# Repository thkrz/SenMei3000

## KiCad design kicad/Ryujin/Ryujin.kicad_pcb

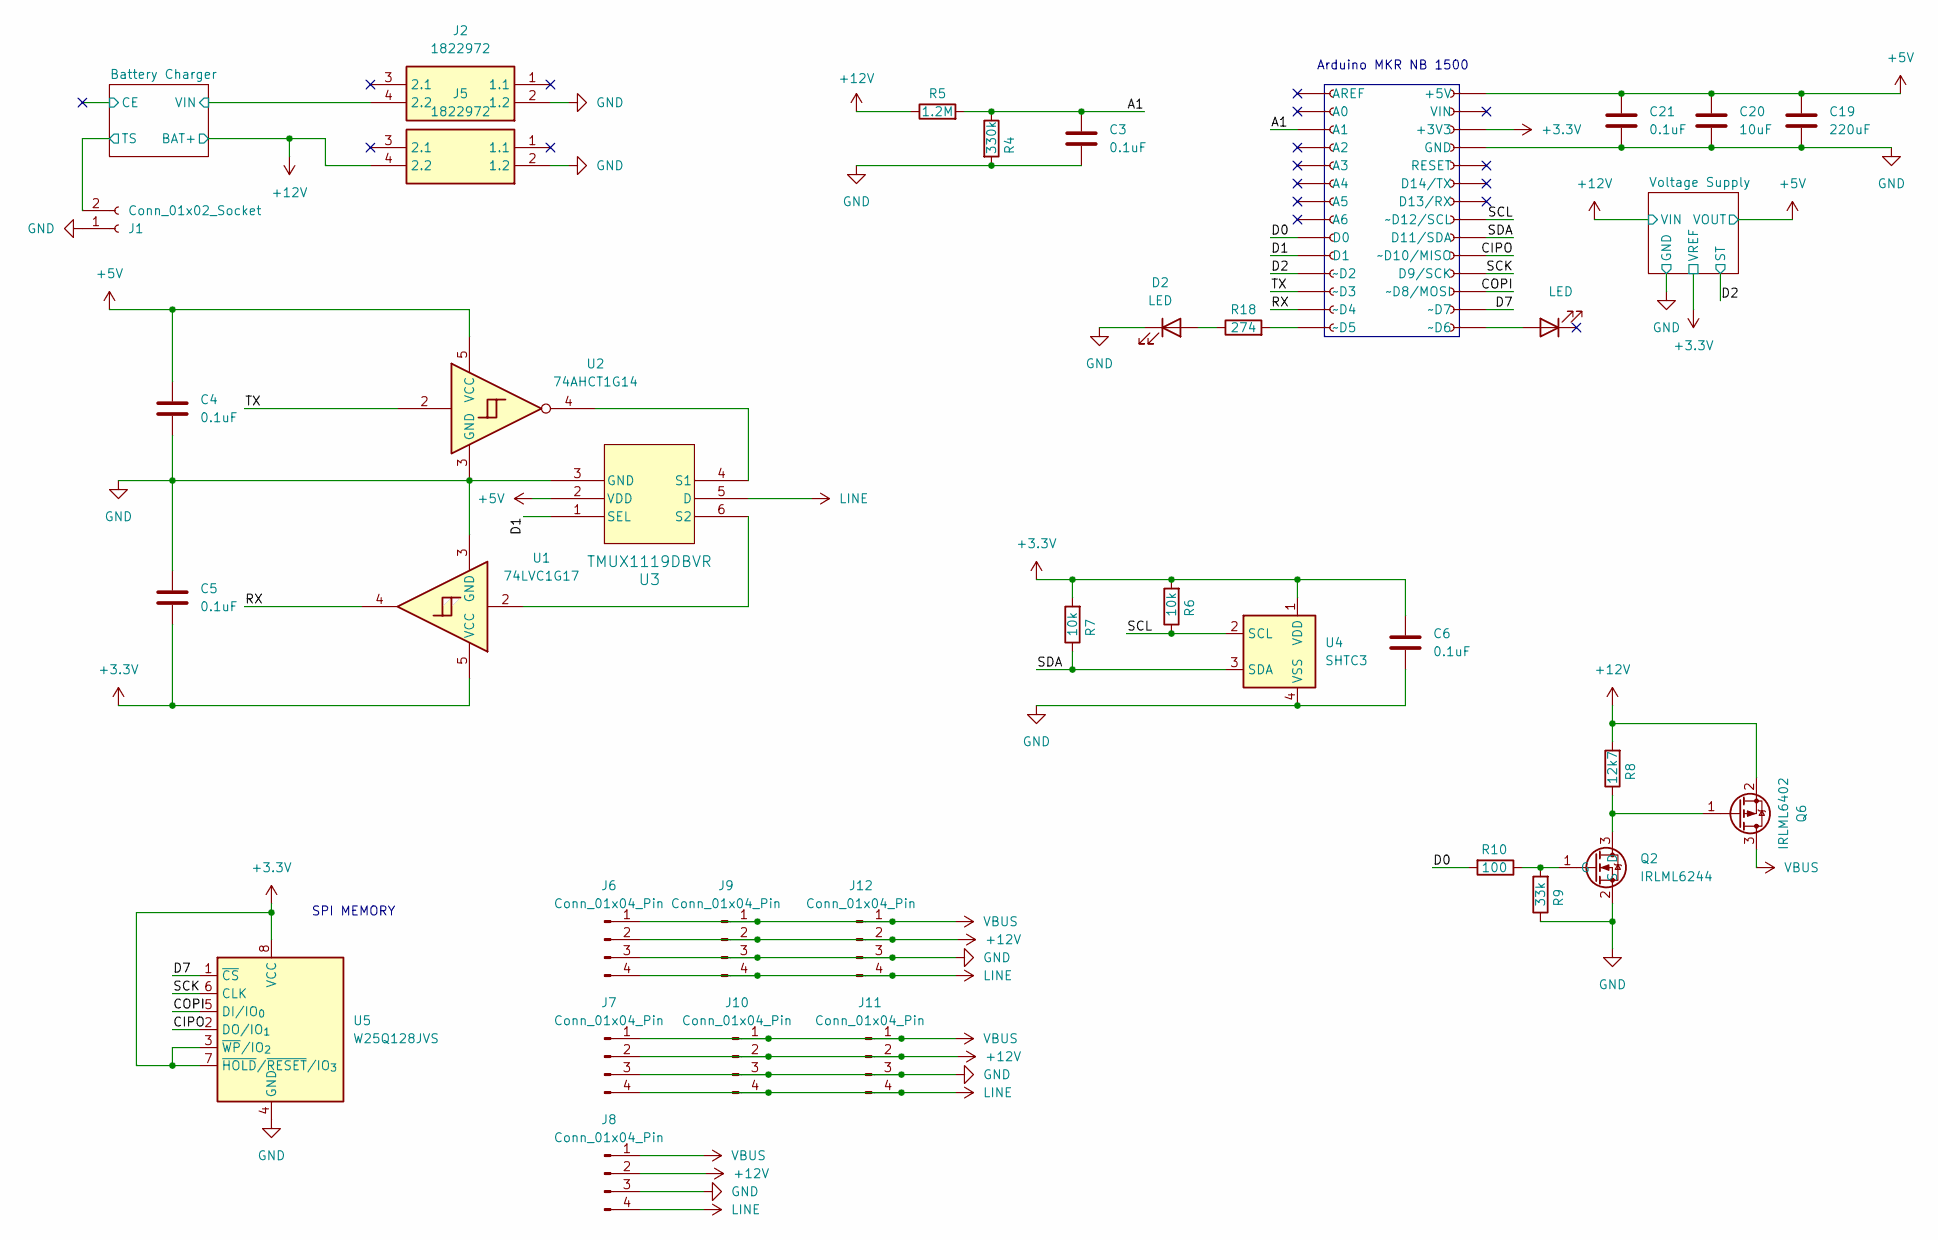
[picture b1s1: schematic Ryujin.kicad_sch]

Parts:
C3, C4, C5, C6, C21: 0.1uF; C_0603_1608Metric; MPN 0.1uF 6.3V 0603
C19: 220uF; EEFCX0J101R; MPN EEFCX0J221R
C20: 10uF; C_0805_2012Metric; MPN 10uF 10V 0805
D2: LED; LED_0603_1608Metric; MPN LTST-C194KFKT
D7: LED; LED_0603_1608Metric
J1: Conn_01x02_Socket; JST_PH_S2B-PH-K_1x02_P2.00mm_Horizontal; MPN S2B-PH-K-S
J2, J5: 1822972; Manufacturer_Part_Number 1822972; Mouser Part Number 651-1822972
J3, J4: Conn_01x14_Socket; 65342372; MPN 6-534237-2
J6, J7, J8, J9, J10, J11, J12: Conn_01x04_Pin; Molex_KK-254_AE-6410-04A_1x04_P2.54mm_Vertical; MPN 22272041
Q2: IRLML6244; SOT-23; MPN IRLML6244TRPBF
Q6: IRLML6402; SOT-23; MPN IRLML6402TRPBF
R4: 330k; R_0603_1608Metric; MPN 330k 0603
R5: 1.2M; R_0603_1608Metric; MPN 1.2M 0603
R6, R7: 10k; R_0603_1608Metric; MPN 10k 0603
R8: 12k7; R_0603_1608Metric; MPN 12.7k 0603
R9: 33k; R_0603_1608Metric; MPN 33k 0603
R10: 100; R_0603_1608Metric; MPN 100 0603
R18: 274; R_0603_1608Metric; MPN 274 0603
U1: 74LVC1G17; SOT-23-5; MPN SN74LVC1G17DBVT
U2: 74AHCT1G14; SOT-23-5; MPN SN74AHCT1G14DBVR
U3: TMUX1119DBVR; TMUXDBVR
U4: SHTC3; Sensirion_DFN-4-1EP_2x2mm_P1mm_EP0.7x1.6mm; MPN SHTC3
U5: W25Q128JVS; SOIC-8_5.3x5.3mm_P1.27mm; MPN W25Q128JVSIQ TR

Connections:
+3.3V: C5.2, C6.1, J4.3 (+3V3), R6.2, R7.2, U1.5 (VCC), U4.1 (VDD), U5.3 (~WP/IO_{2}), U5.7 (~HOLD/~RESET/IO_{3}), U5.8 (VCC); also elsewhere on the board
+5V: C4.1, C19.1, C20.1, C21.1, J4.1 (+5V), U2.5 (VCC), U3.2 (VDD); also elsewhere on the board
+12V: J5.4 (2.2), J6.2, J7.2, J8.2, J9.2, J10.2, J11.2, J12.2, Q6.2 (S), R5.1, R8.2; also elsewhere on the board
/A1: C3.1, J3.3 (A1), R4.1, R5.2
/Battery Charger/TS: J1.2; also elsewhere on the board
/Battery Charger/VIN: J2.4 (2.2); also elsewhere on the board
/CIPO: J4.10 (~D10/MISO), U5.2 (DO/IO_{1})
/COPI: J4.12 (~D8/MOSI), U5.5 (DI/IO_{0})
/D0: J3.9 (D0), R10.2
/D1: J3.10 (D1), U3.1 (SEL)
/D2: J3.11 (~D2); also elsewhere on the board
/D7: J4.13 (~D7), U5.1 (~CS)
/RX: J3.13 (~D4), U1.4
/SCK: J4.11 (D9/SCK), U5.6 (CLK)
/SCL: J4.8 (~D12/SCL), R6.1, U4.2 (SCL)
/SDA: J4.9 (D11/SDA), R7.1, U4.3 (SDA)
/TX: J3.12 (~D3), U2.2
GND: C3.2, C4.2, C5.1, C6.2, C19.2, C20.2, C21.2, D2.1 (K), J1.1, J2.2 (1.2), J4.4 (GND), J5.2 (1.2), J6.3, J7.3, J8.3, J9.3, J10.3, J11.3, J12.3, Q2.2 (S), R4.2, R9.1, U1.3 (GND), U2.3 (GND), U3.3 (GND), U4.4 (VSS), U5.4 (GND); also elsewhere on the board
LINE: J6.4, J7.4, J8.4, J9.4, J10.4, J11.4, J12.4, U3.5 (D)
unnamed: D2.2 (A), R18.1
unnamed: J3.14 (~D5), R18.2
unnamed: D7.2 (A), J4.14 (~D6)
unnamed: Q2.3 (D), Q6.1 (G), R8.1
unnamed: Q2.1 (G), R9.2, R10.1
unnamed: U2.4, U3.4 (S1)
unnamed: U1.2, U3.6 (S2)
VBUS: J6.1, J7.1, J8.1, J9.1, J10.1, J11.1, J12.1, Q6.3 (D)

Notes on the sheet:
SPI MEMORY
Arduino MKR NB 1500

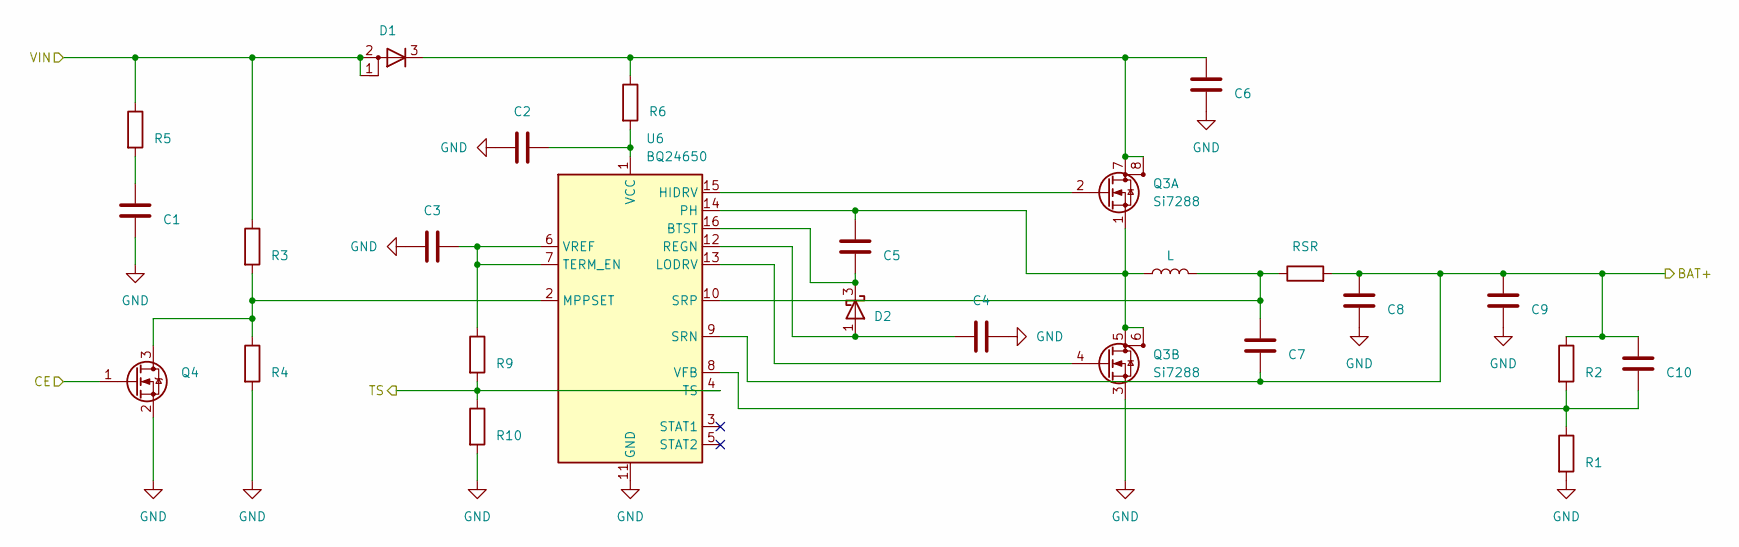
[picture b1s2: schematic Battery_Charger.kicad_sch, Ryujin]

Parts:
C7: C1; C_1210_3225Metric; MPN 2.2uF 50V 1210
C8: C2; C_0805_2012Metric; MPN 1uF 35V 0805
C9: C6; C_1210_3225Metric; MPN 10uF 35V 1210
C10: C4; C_0805_2012Metric; MPN 1uF 35V 0805
C11: C5; C_0805_2012Metric; MPN C0805C104K6RACTU
C12: C8; C_1210_3225Metric; MPN 10uF 35V 1210
C13: C7; C_0805_2012Metric; MPN C0805C104K6RACTU
C14: C10; C_0603_1608Metric; MPN 22pF 50V 0603
C15: C3; C_0805_2012Metric; MPN 1uF 35V 0805
C16: C9; C_Elec_4x5.4; MPN EEEFK1V4R7AR
D5: D1; PDS104013; MPN PDS1040-13
D6: D2; SOT-23; MPN BAT54
L1: L; L_Vishay_IHLP-2525; MPN IHLP2525CZER100MA1
Q3: Si7288; SI7288DPT1GE3; MPN SI7288DP-T1-GE3
Q4: 2N7002; SOT-23
R1: R5; R_2512_6332Metric; MPN 2 5% 1W
R2: R3; R_0402_1005Metric; MPN 499k 0402
R3: R4; R_0402_1005Metric; MPN 36k 0402
R13: R6; R_1206_3216Metric; MPN 10 1206 0.25W
R14: R9; R_0402_1005Metric; MPN 5.23k 0402
R15: R1; R_0402_1005Metric; MPN 97.6k 0402
R16: R2; R_0402_1005Metric; MPN 536k 0402
R17: R10; R_0402_1005Metric; MPN 30.1k 0402
RSR1: RSR; R_1206_3216Metric; MPN WSL1206R0200DEA
U6: BQ24650; Texas_RVA_VQFN-16-1EP_3.5x3.5mm_P0.5mm_EP2.14x2.14mm_Therma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; MPN BQ24650RVAR

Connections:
+12V: C12.1, C13.1, C14.1, C16.1, R16.1, RSR1.2, U6.9 (SRN); also elsewhere on the board
/Battery Charger/TS: R14.2, R17.1, U6.4 (TS); also elsewhere on the board
/Battery Charger/VIN: D5.1 (A), D5.2 (A), R1.1, R2.1; also elsewhere on the board
GND: C7.2, C8.1, C9.2, C10.2, C12.2, C15.1, C16.2, Q3.3 (S), Q4.2 (S), R3.2, R15.2, R17.2, U6.11 (GND), U6.17 (GND); also elsewhere on the board
unnamed: C7.1, R1.2
unnamed: C9.1, D5.3 (K), Q3.7 (D), Q3.8 (D), Q3.9 (D), Q3.11 (D), R13.1
unnamed: C10.1, D6.1 (A), U6.12 (REGN)
unnamed: C11.1, D6.3 (K), U6.16 (BTST)
unnamed: Q3.2 (G), U6.15 (HIDRV)
unnamed: C11.2, L1.1, Q3.1 (S), Q3.5 (D), Q3.6 (D), Q3.10 (D), Q3.12 (D), U6.14 (PH)
unnamed: Q3.4 (G), U6.13 (LODRV)
unnamed: Q4.3 (D), R2.2, R3.1, U6.2 (MPPSET)
unnamed: C13.2, L1.2, RSR1.1, U6.10 (SRP)
unnamed: C15.2, R14.1, U6.6 (VREF), U6.7 (TERM_EN)
unnamed: C8.2, R13.2, U6.1 (VCC)
unnamed: C14.2, R15.1, R16.2, U6.8 (VFB)

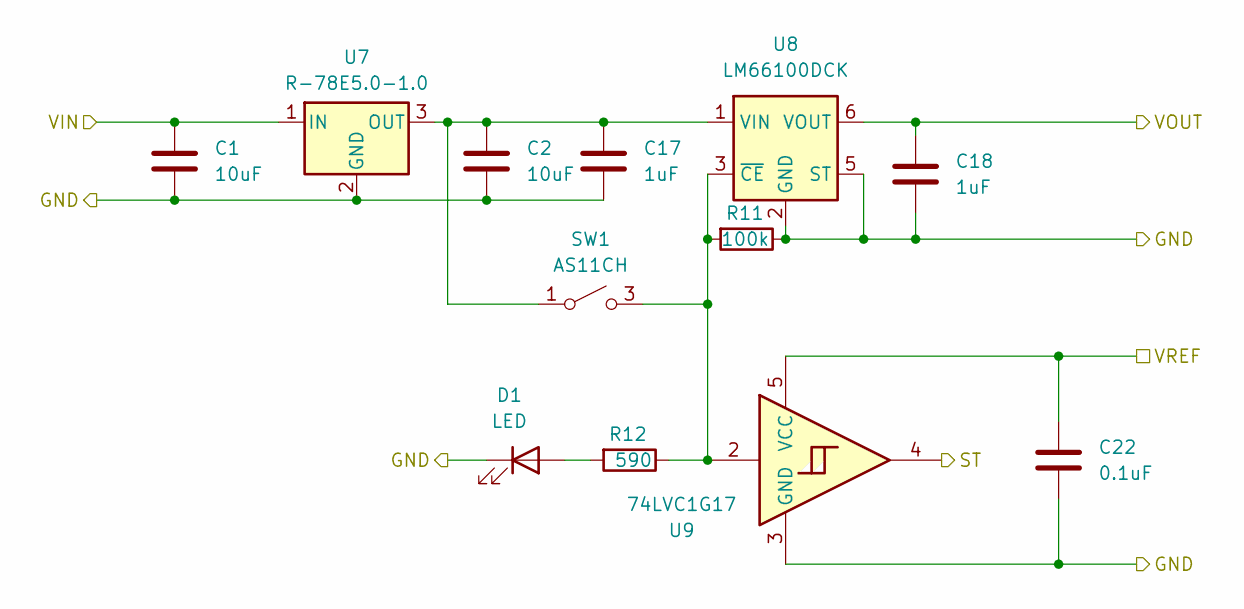
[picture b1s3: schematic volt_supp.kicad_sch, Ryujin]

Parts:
C1: 10uF; C_1206_3216Metric; MPN 10uF 16V 1206
C2: 10uF; C_0805_2012Metric; MPN 10uF 6.3V 0805
C17, C18: 1uF; C_0603_1608Metric; MPN 1uF 6.3V 0603
C22: 0.1uF; C_0603_1608Metric; MPN 0.1uF 6.3V 0603
D1: LED; LED_0603_1608Metric; MPN LTST-C193KRKT-5A
R11: 100k; R_0603_1608Metric; MPN 100k 0603
R12: 590; R_0603_1608Metric; MPN 590 0603
SW1: AS11CH
U7: R-78E5.0-1.0; Converter_DCDC_RECOM_R-78E-0.5_THT
U8: LM66100DCK; SOT-363_SC-70-6; MPN LM66100DCKT
U9: 74LVC1G17; SOT-23-5; MPN SN74LVC1G17DBVT

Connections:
+3.3V: C22.2, U9.5 (VCC); also elsewhere on the board
+5V: C18.1, U8.6 (VOUT); also elsewhere on the board
+12V: C1.1, U7.1 (IN); also elsewhere on the board
/D2: U9.4; also elsewhere on the board
GND: C1.2, C2.2, C17.2, C18.2, C22.1, D1.1 (K), R11.1, U7.2 (GND), U8.2 (GND), U8.5 (ST), U9.3 (GND); also elsewhere on the board
unnamed: D1.2 (A), R12.2
unnamed: C2.1, C17.1, SW1.1 (A), U7.3 (OUT), U8.1 (VIN)
unnamed: R11.2, R12.1, SW1.3 (B), U8.3 (~CE), U9.2

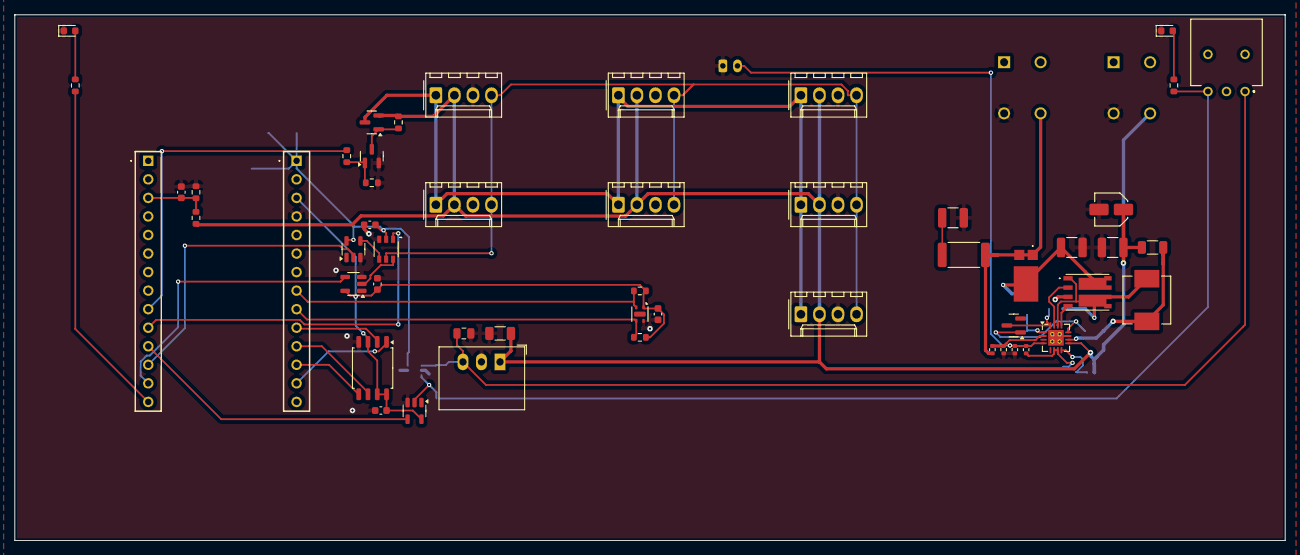
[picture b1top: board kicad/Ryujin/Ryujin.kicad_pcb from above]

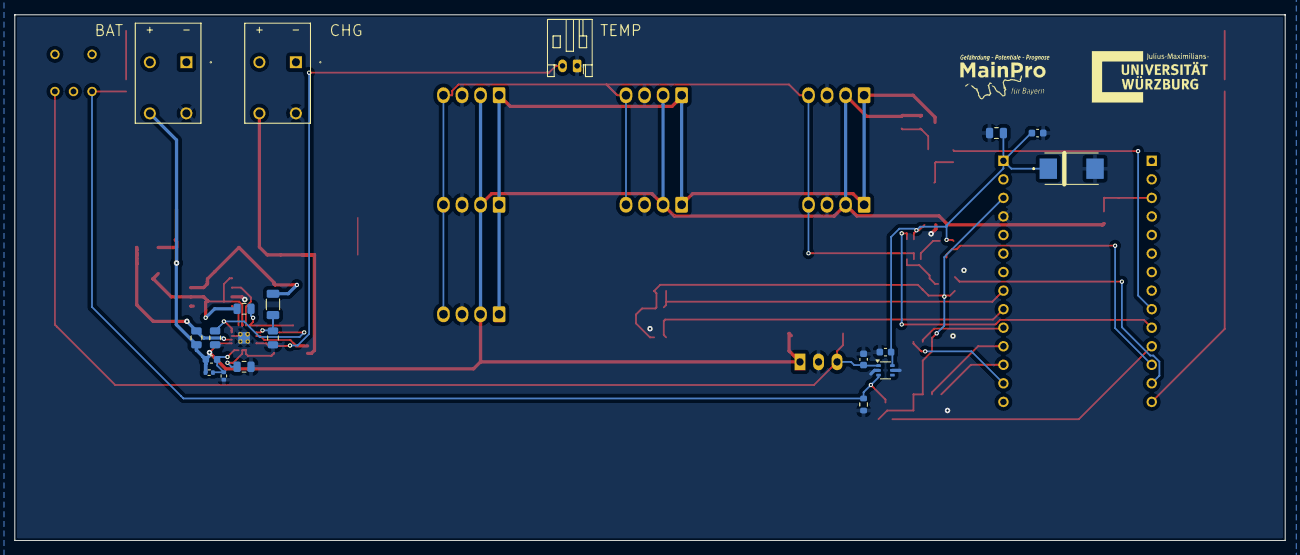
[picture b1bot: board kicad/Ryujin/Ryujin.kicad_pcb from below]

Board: 2 copper layers, 174.0 x 72.0 mm, 73 parts (21 on the bottom side), 41 nets.

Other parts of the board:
G1, G2: LOGO

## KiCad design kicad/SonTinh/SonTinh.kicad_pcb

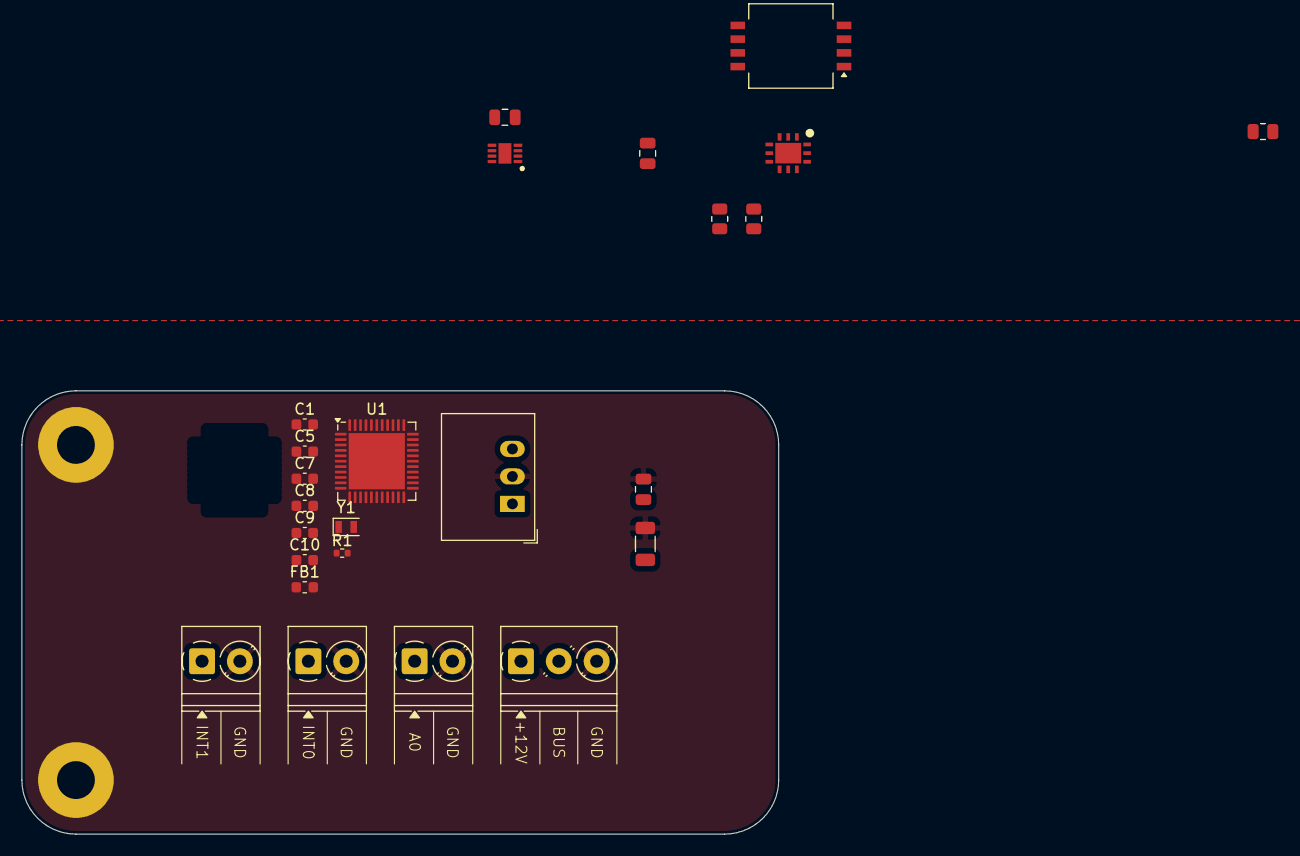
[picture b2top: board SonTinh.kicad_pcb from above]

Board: 2 copper layers, 70.0 x 41.0 mm, 27 parts (0 on the bottom side), 10 nets, no tracks yet.

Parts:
C1, C5, C7, C8, C9, C10: C; C_0603_1608Metric
C2, C6: C; C_0805_2012Metric
C3: 10uF; C_1206_3216Metric
C4: 10uF; C_0805_2012Metric
FB1: FerriteBead; L_0603_1608Metric
H1, H2: MountingHole_Pad; MountingHole_3.5mm_Pad
IC1: SHT35-DIS-F2.5kS; SON50P250X250X100-9N-D
IC2: STC31-C-R3; QFN80P300X350X110-13N-D
J1, J2, J3: Screw_Terminal_01x02; TerminalBlock_Phoenix_PT-1,5-2-3.5-H_1x02_P3.50mm_Horizontal
J4: Screw_Terminal_01x03; TerminalBlock_Phoenix_PT-1,5-3-3.5-H_1x03_P3.50mm_Horizontal
R1: R; R_0402_1005Metric
R13: 100k; R_0805_2012Metric
R14, R15: 10k; R_0805_2012Metric
U1: ATmega32U4-M; QFN-44-1EP_7x7mm_P0.5mm_EP5.2x5.2mm
U3: MPXH6115A; Freescale_98ARH99066A
U7: R-78E5.0-1.0; Converter_DCDC_RECOM_R-78E-0.5_THT
Y1: Crystal; Crystal_SMD_2012-2Pin_2.0x1.2mm

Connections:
+5V: C2.2, C4.1, C6.2, IC1.5 (VDD), IC2.6 (VDD), R14.2, R15.2, U3.2 (Vcc), U7.3 (OUT)
+12V: C3.1, J4.1, U7.1 (IN)
/D7: J4.2, R13.2
/MCU/GND: C1.2, C5.2, C7.2, C8.2, C9.2, C10.2, R1.1, U1.5 (UGND), U1.15 (GND), U1.23 (GND), U1.35 (GND), U1.43 (GND), U1.45 (GND)
/MCU/VCC: C1.1, C5.1, C7.1, C8.1, C10.1, FB1.1, FB1.2, U1.2 (UVCC), U1.14 (VCC), U1.24 (AVCC), U1.34 (VCC), U1.44 (AVCC)
/SCL_5V: IC1.4 (SCL), IC2.4 (SCL), R14.1
/SDA_5V: IC1.1 (SDA), IC2.7 (SDA), R15.1
GND: C2.1, C3.2, C4.2, C6.1, H1.1, H2.1, IC1.2 (ADDR), IC1.7 (R), IC1.8 (VSS), IC1.9 (EP), IC2.1 (VSS_1), IC2.3 (ADDR), IC2.5 (VSS_2), IC2.9 (VSS_3), IC2.11 (VSS_4), IC2.13 (EP), J1.2, J2.2, J3.2, J4.3, R13.1, U3.3 (GND), U7.2 (GND)
unnamed: C9.1, U1.42 (AREF)
unnamed: R1.2, U1.13 (~RESET)

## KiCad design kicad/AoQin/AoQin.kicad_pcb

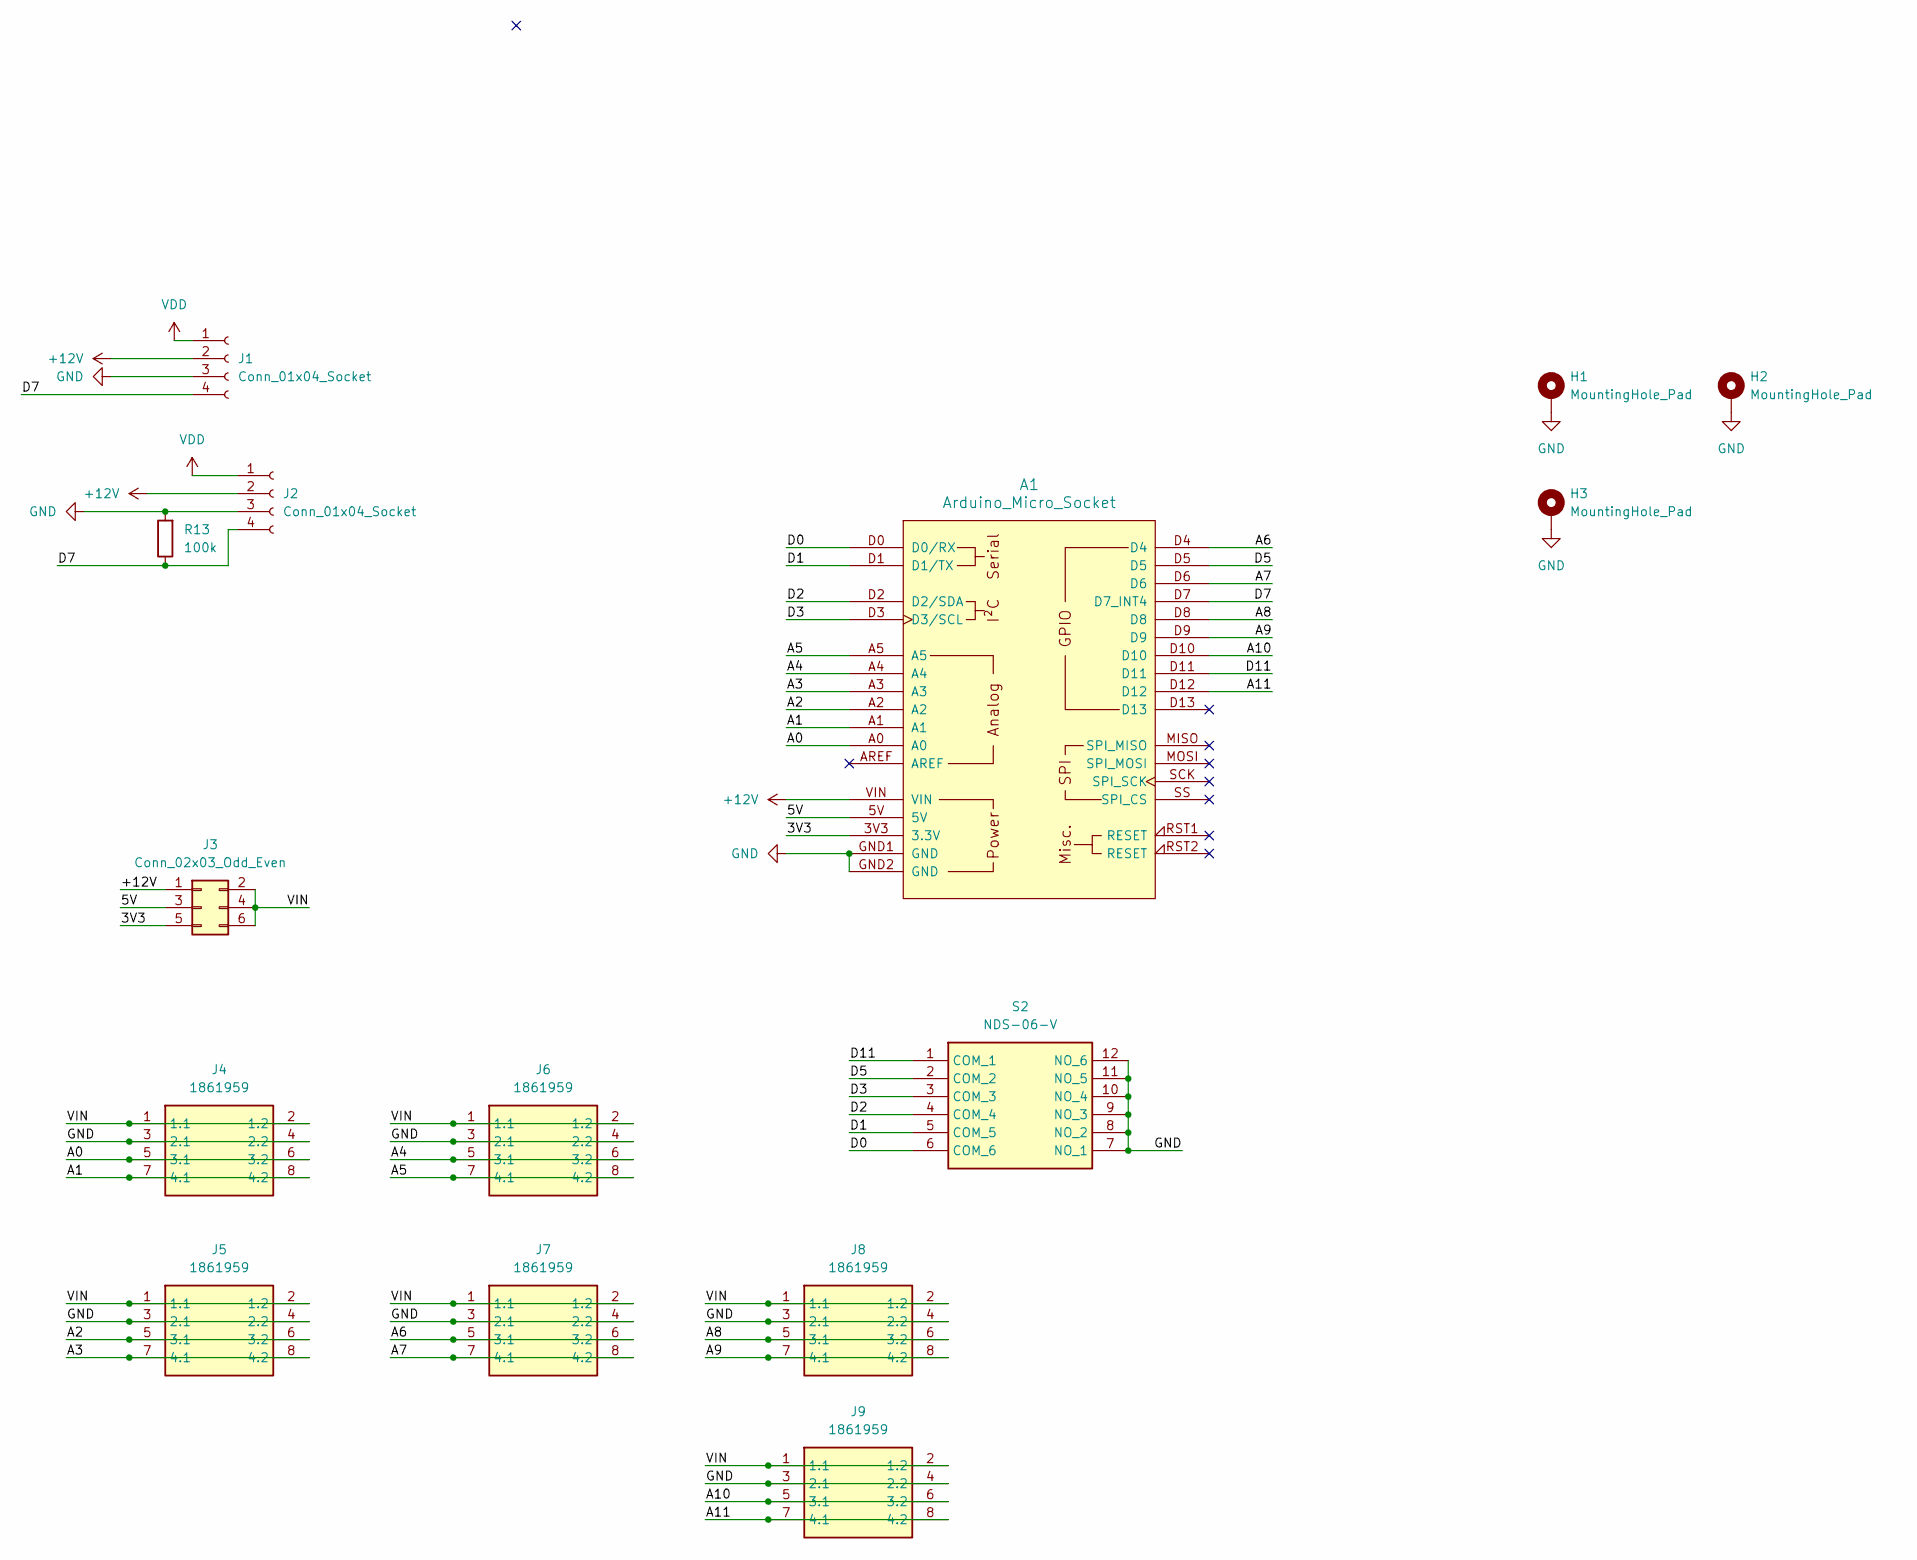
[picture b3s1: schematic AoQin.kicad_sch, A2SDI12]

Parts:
A1: Arduino_Micro_Socket
H1, H2, H3: MountingHole_Pad; MountingHole_3.5mm_Pad
J1, J2: Conn_01x04_Socket; SolderWire-0.5sqmm_1x04_P4.6mm_D0.9mm_OD2.1mm
J3: Conn_02x03_Odd_Even; PinHeader_2x03_P2.54mm_Vertical
J4, J5, J6, J7, J8, J9: 1861959; Manufacturer_Part_Number 1861959; Mouser Part Number 651-1861959
R13: 100k; R_Axial_DIN0204_L3.6mm_D1.6mm_P7.62mm_Horizontal; MPN 100k
S2: NDS-06-V; NDS06V; Manufacturer_Part_Number NDS-06-V; Mouser Part Number N/A

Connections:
+12V: A1.VIN, J1.2, J2.2, J3.1
/3V3: A1.3V3 (3.3V), J3.5
/5V: A1.5V, J3.3
/A0: A1.A0, J4.5 (3.1), J4.6 (3.2)
/A1: A1.A1, J4.7 (4.1), J4.8 (4.2)
/A2: A1.A2, J5.5 (3.1), J5.6 (3.2)
/A3: A1.A3, J5.7 (4.1), J5.8 (4.2)
/A4: A1.A4, J6.5 (3.1), J6.6 (3.2)
/A5: A1.A5, J6.7 (4.1), J6.8 (4.2)
/A6: A1.D4, J7.5 (3.1), J7.6 (3.2)
/A7: A1.D6, J7.7 (4.1), J7.8 (4.2)
/A8: A1.D8, J8.5 (3.1), J8.6 (3.2)
/A9: A1.D9, J8.7 (4.1), J8.8 (4.2)
/A10: A1.D10, J9.5 (3.1), J9.6 (3.2)
/A11: A1.D12, J9.7 (4.1), J9.8 (4.2)
/D0: A1.D0 (D0/RX), S2.6 (COM_6)
/D1: A1.D1 (D1/TX), S2.5 (COM_5)
/D2: A1.D2 (D2/SDA), S2.4 (COM_4)
/D3: A1.D3 (D3/SCL), S2.3 (COM_3)
/D5: A1.D5, S2.2 (COM_2)
/D7: A1.D7 (D7_INT4), J1.4, J2.4, R13.1
/D11: A1.D11, S2.1 (COM_1)
/VIN: J3.2, J3.4, J3.6, J4.1 (1.1), J4.2 (1.2), J5.1 (1.1), J5.2 (1.2), J6.1 (1.1), J6.2 (1.2), J7.1 (1.1), J7.2 (1.2), J8.1 (1.1), J8.2 (1.2), J9.1 (1.1), J9.2 (1.2)
GND: A1.GND1 (GND), A1.GND2 (GND), H1.1, H2.1, H3.1, J1.3, J2.3, J4.3 (2.1), J4.4 (2.2), J5.3 (2.1), J5.4 (2.2), J6.3 (2.1), J6.4 (2.2), J7.3 (2.1), J7.4 (2.2), J8.3 (2.1), J8.4 (2.2), J9.3 (2.1), J9.4 (2.2), R13.2, S2.7 (NO_1), S2.8 (NO_2), S2.9 (NO_3), S2.10 (NO_4), S2.11 (NO_5), S2.12 (NO_6)
VDD: J1.1, J2.1

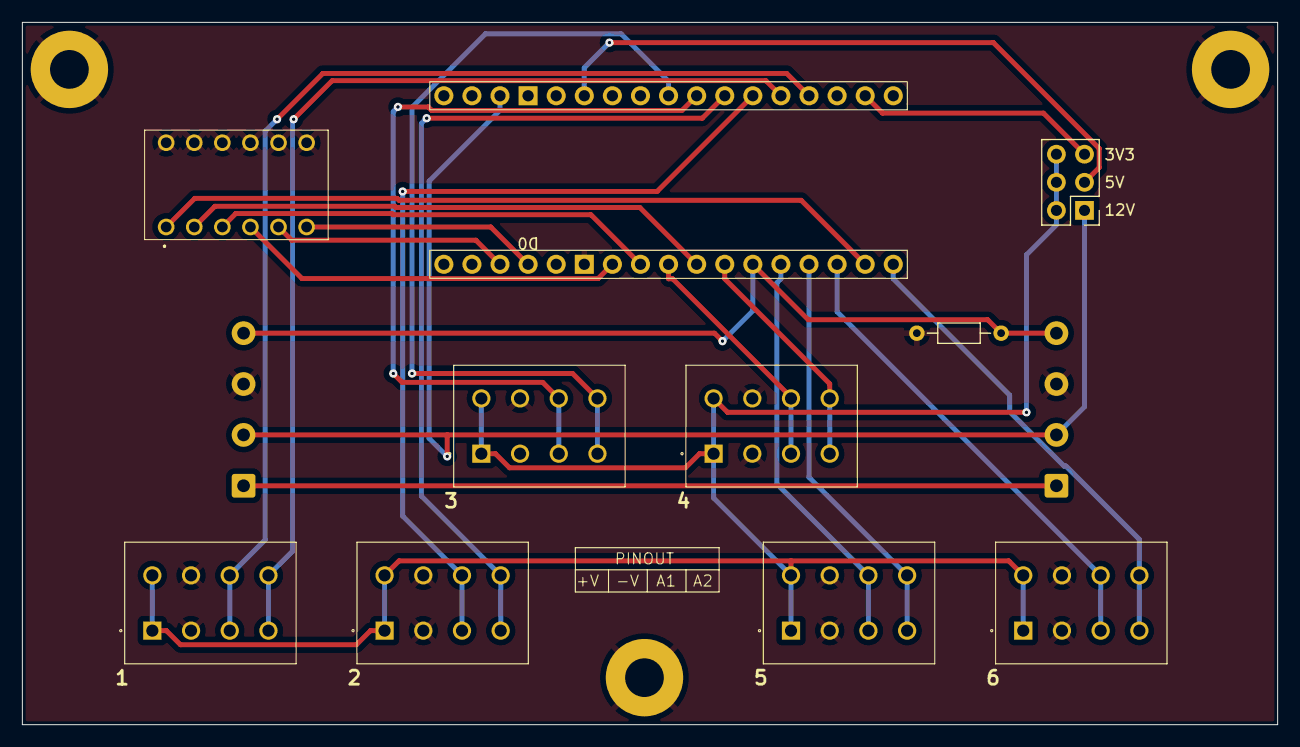
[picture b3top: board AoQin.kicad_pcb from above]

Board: 2 copper layers, 113.5 x 63.5 mm, 15 parts (0 on the bottom side), 25 nets.

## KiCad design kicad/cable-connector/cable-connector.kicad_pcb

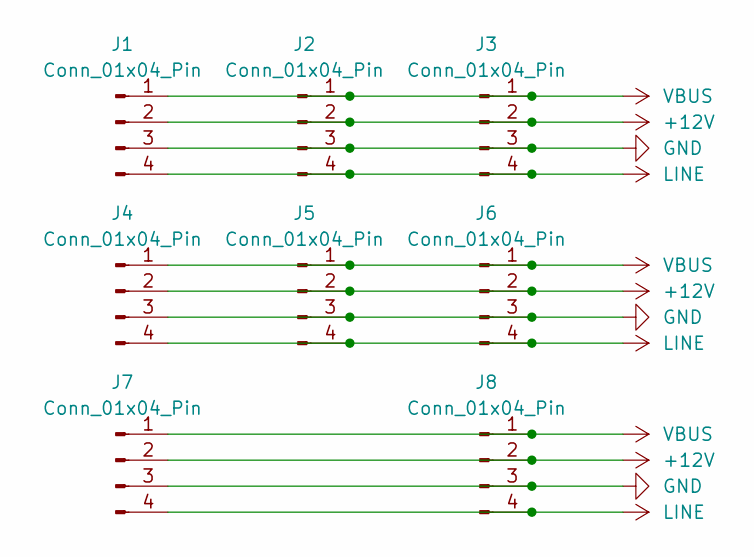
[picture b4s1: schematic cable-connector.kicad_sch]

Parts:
J1, J2, J3, J4, J5, J6, J7: Conn_01x04_Pin; SDI_Connector
J8: Conn_01x04_Pin; GROVE-HW4-2.0

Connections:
+12V: J1.2, J2.2, J3.2, J4.2, J5.2, J6.2, J7.2, J8.2
GND: J1.3, J2.3, J3.3, J4.3, J5.3, J6.3, J7.3, J8.3
LINE: J1.4, J2.4, J3.4, J4.4, J5.4, J6.4, J7.4, J8.4
VBUS: J1.1, J2.1, J3.1, J4.1, J5.1, J6.1, J7.1, J8.1

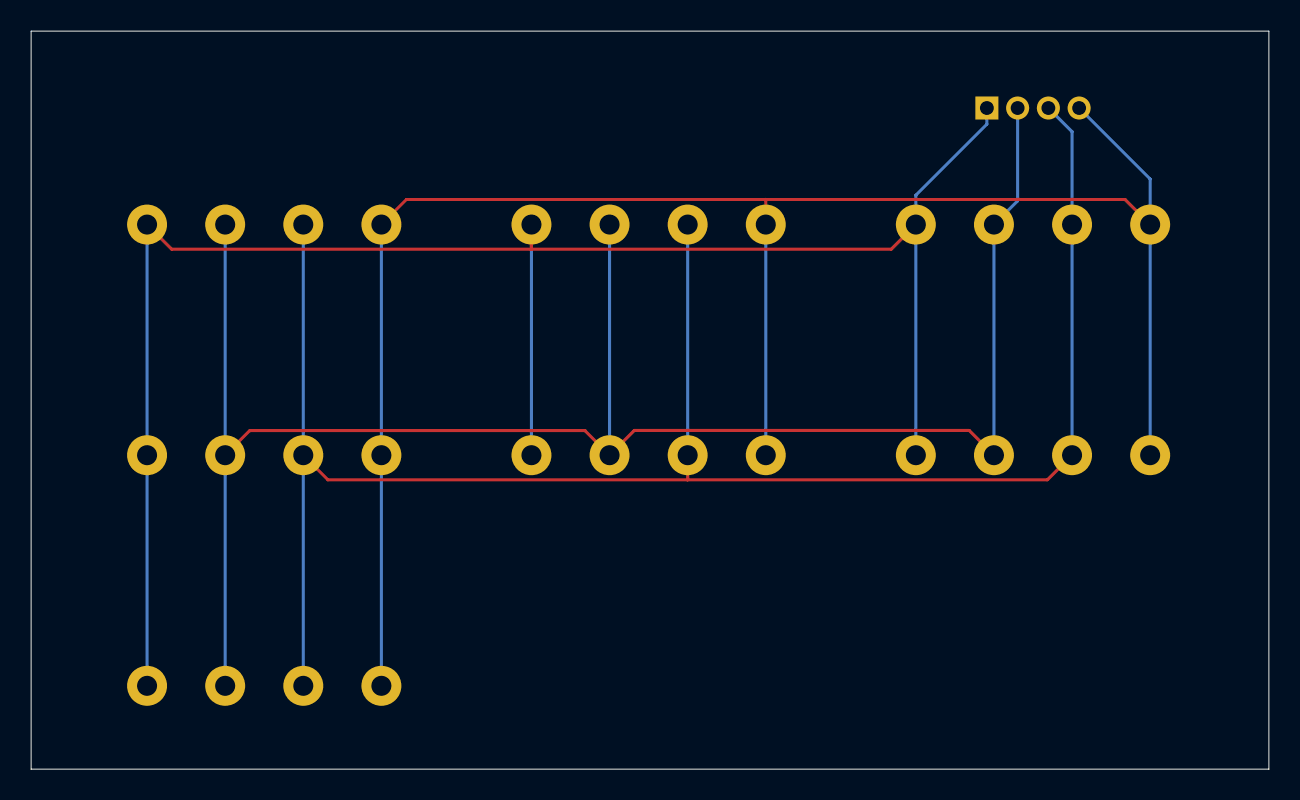
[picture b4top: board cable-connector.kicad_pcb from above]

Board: 2 copper layers, 80.5 x 48.0 mm, 8 parts (1 on the bottom side), 4 nets.

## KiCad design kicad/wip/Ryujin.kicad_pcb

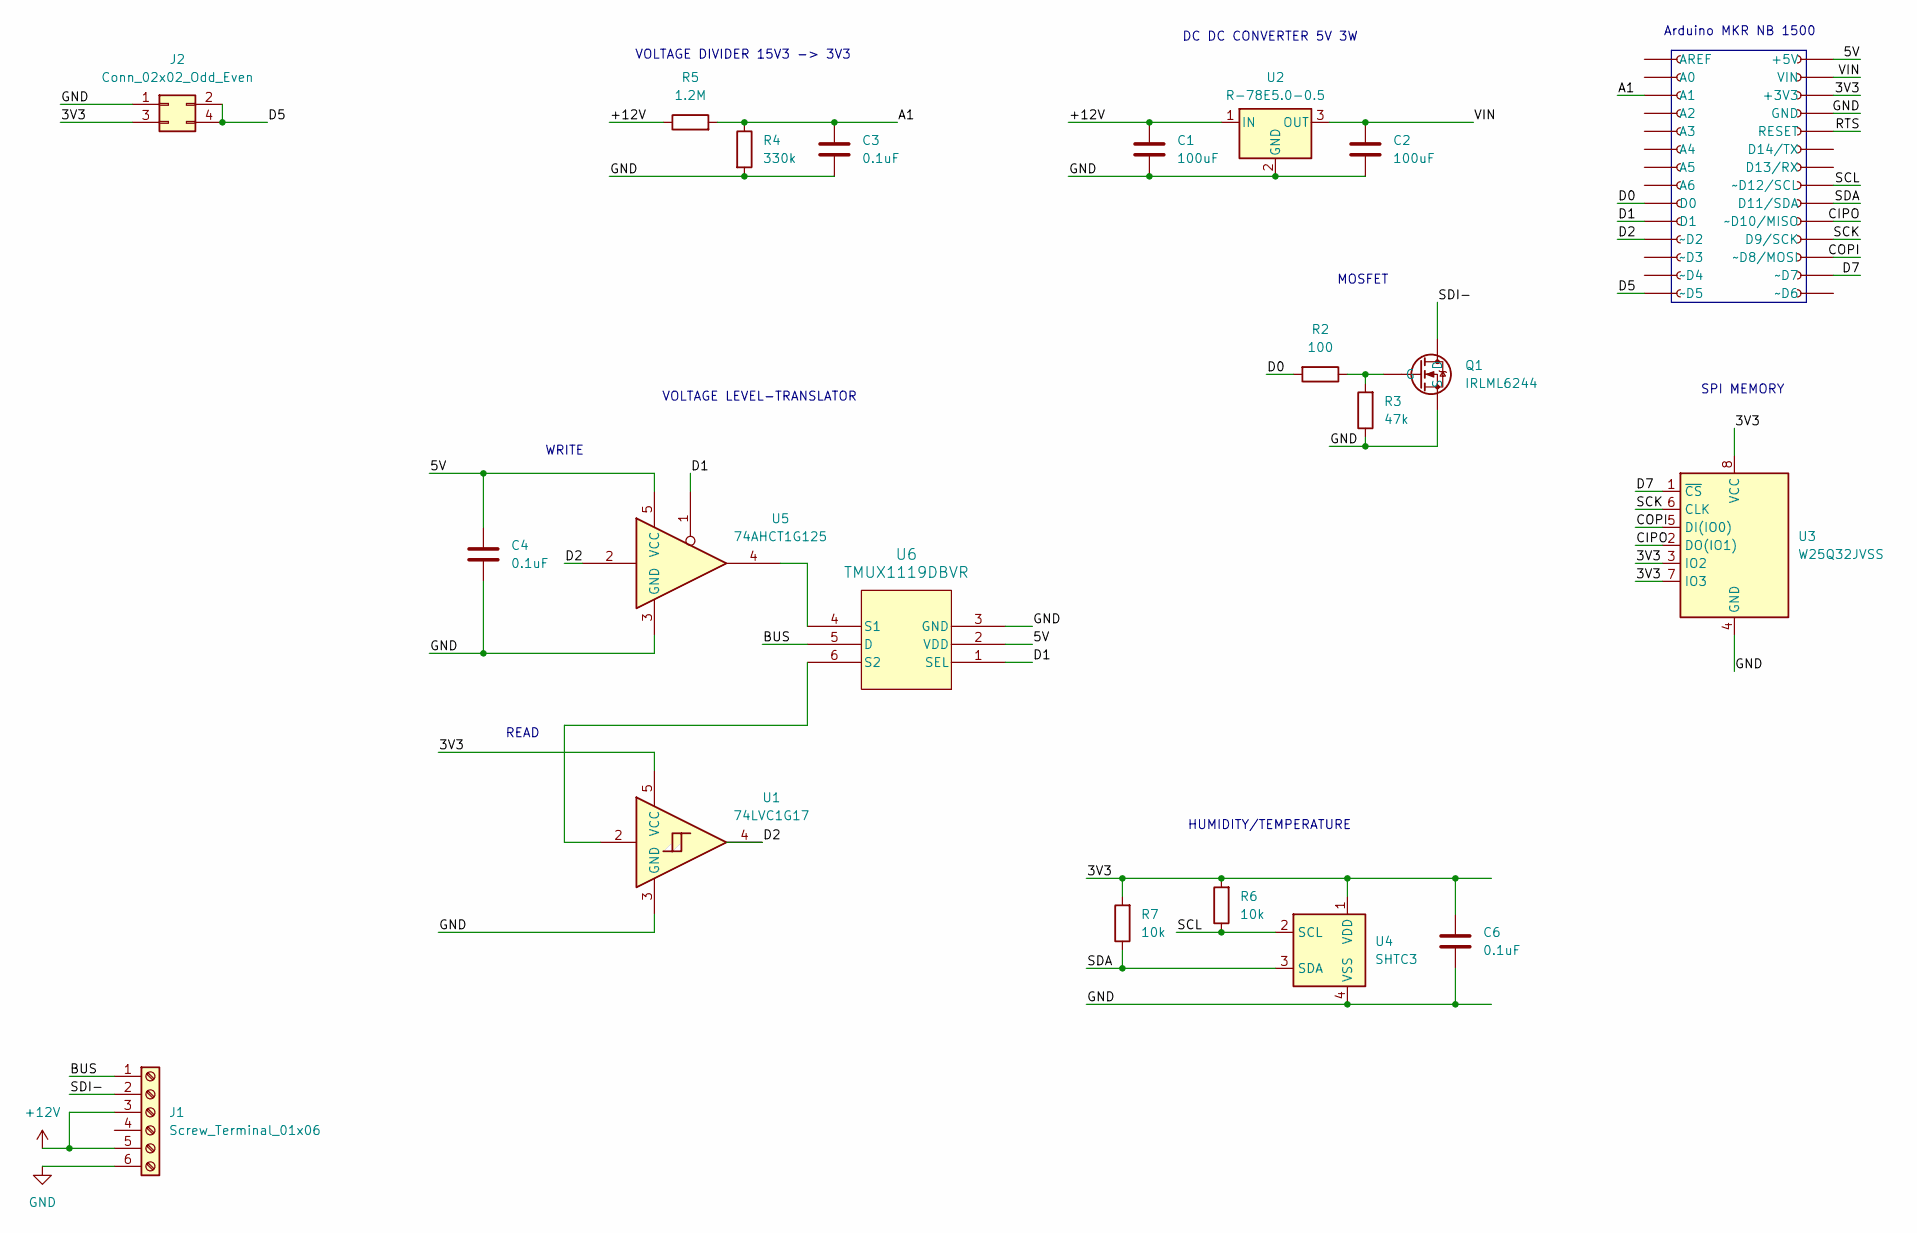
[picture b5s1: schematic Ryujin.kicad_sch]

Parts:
C1: 100uF; C_1210_3225Metric; MPN C1210C107M4PACTU
C2: 100uF; C_1210_3225Metric; MPN C1210C107M9PACTU
C3, C4, C6: 0.1uF; C_0603_1608Metric; MPN 0.1uF 6.3V 0603
J1: Screw_Terminal_01x06; SMKDSN-1-5-6-5-08_3D; MPN 1869253
J2: Conn_02x02_Odd_Even; HDRV4W85P254_2X2_508X500X970P; MPN 826632-2
J3, J4: Conn_01x14_Socket; 65342372; MPN 6-534237-2
Q1: IRLML6244; SOT-23; MPN IRLML6244TRPBF
R2: 100; R_0603_1608Metric; MPN 100 0603
R3: 47k; R_0603_1608Metric; MPN 47k 0603
R4: 330k; R_0603_1608Metric; MPN 330k 0603
R5: 1.2M; R_0603_1608Metric; MPN 1.2M 0603
R6, R7: 10k; R_0603_1608Metric; MPN 10k 0603
U1: 74LVC1G17; SOT-23-5; MPN SN74LVC1G17DBVT
U2: R-78E5.0-0.5; Converter_DCDC_RECOM_R-78E-0.5_THT; MPN R-78E5.0-0.5
U3: W25Q32JVSS; SOIC-8_5.23x5.23mm_P1.27mm; MPN W25Q32JVSSIQ TR
U4: SHTC3; Sensirion_DFN-4-1EP_2x2mm_P1mm_EP0.7x1.6mm; MPN SHTC3
U5: 74AHCT1G125; SOT-23-5; MPN SN74AHCT1G125DBVR
U6: TMUX1119DBVR; TMUXDBVR

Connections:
+12V: C1.1, J1.3, J1.5, R5.1, U2.1 (IN)
/3V3: C6.1, J2.3, J4.3 (+3V3), R6.2, R7.2, U1.5 (VCC), U3.3 (IO2), U3.7 (IO3), U3.8 (VCC), U4.1 (VDD)
/5V: C4.1, J4.1 (+5V), U5.5 (VCC), U6.2 (VDD)
/A1: C3.1, J3.3 (A1), R4.1, R5.2
/BUS: J1.1, U6.5 (D)
/CIPO: J4.10 (~D10/MISO), U3.2 (DO(IO1))
/COPI: J4.12 (~D8/MOSI), U3.5 (DI(IO0))
/D0: J3.9 (D0), R2.2
/D1: J3.10 (D1), U5.1, U6.1 (SEL)
/D2: J3.11 (~D2), U1.4, U5.2
/D5: J2.2, J2.4, J3.14 (~D5)
/D7: J4.13 (~D7), U3.1 (~CS)
/RTS: J4.5 (RESET)
/SCK: J4.11 (D9/SCK), U3.6 (CLK)
/SCL: J4.8 (~D12/SCL), R6.1, U4.2 (SCL)
/SDA: J4.9 (D11/SDA), R7.1, U4.3 (SDA)
/SDI-: J1.2, Q1.3 (D)
/VIN: C2.1, J4.2 (VIN), U2.3 (OUT)
GND: C1.2, C2.2, C3.2, C4.2, C6.2, J1.6, J2.1, J4.4 (GND), Q1.2 (S), R3.1, R4.2, U1.3 (GND), U2.2 (GND), U3.4 (GND), U4.4 (VSS), U5.3 (GND), U6.3 (GND)
unnamed: Q1.1 (G), R2.1, R3.2
unnamed: U5.4, U6.4 (S1)
unnamed: U1.2, U6.6 (S2)

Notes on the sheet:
HUMIDITY/TEMPERATURE
VOLTAGE LEVEL-TRANSLATOR
WRITE
VOLTAGE DIVIDER 15V3 -> 3V3
SPI MEMORY
READ
Arduino MKR NB 1500
DC DC CONVERTER 5V 3W
MOSFET
